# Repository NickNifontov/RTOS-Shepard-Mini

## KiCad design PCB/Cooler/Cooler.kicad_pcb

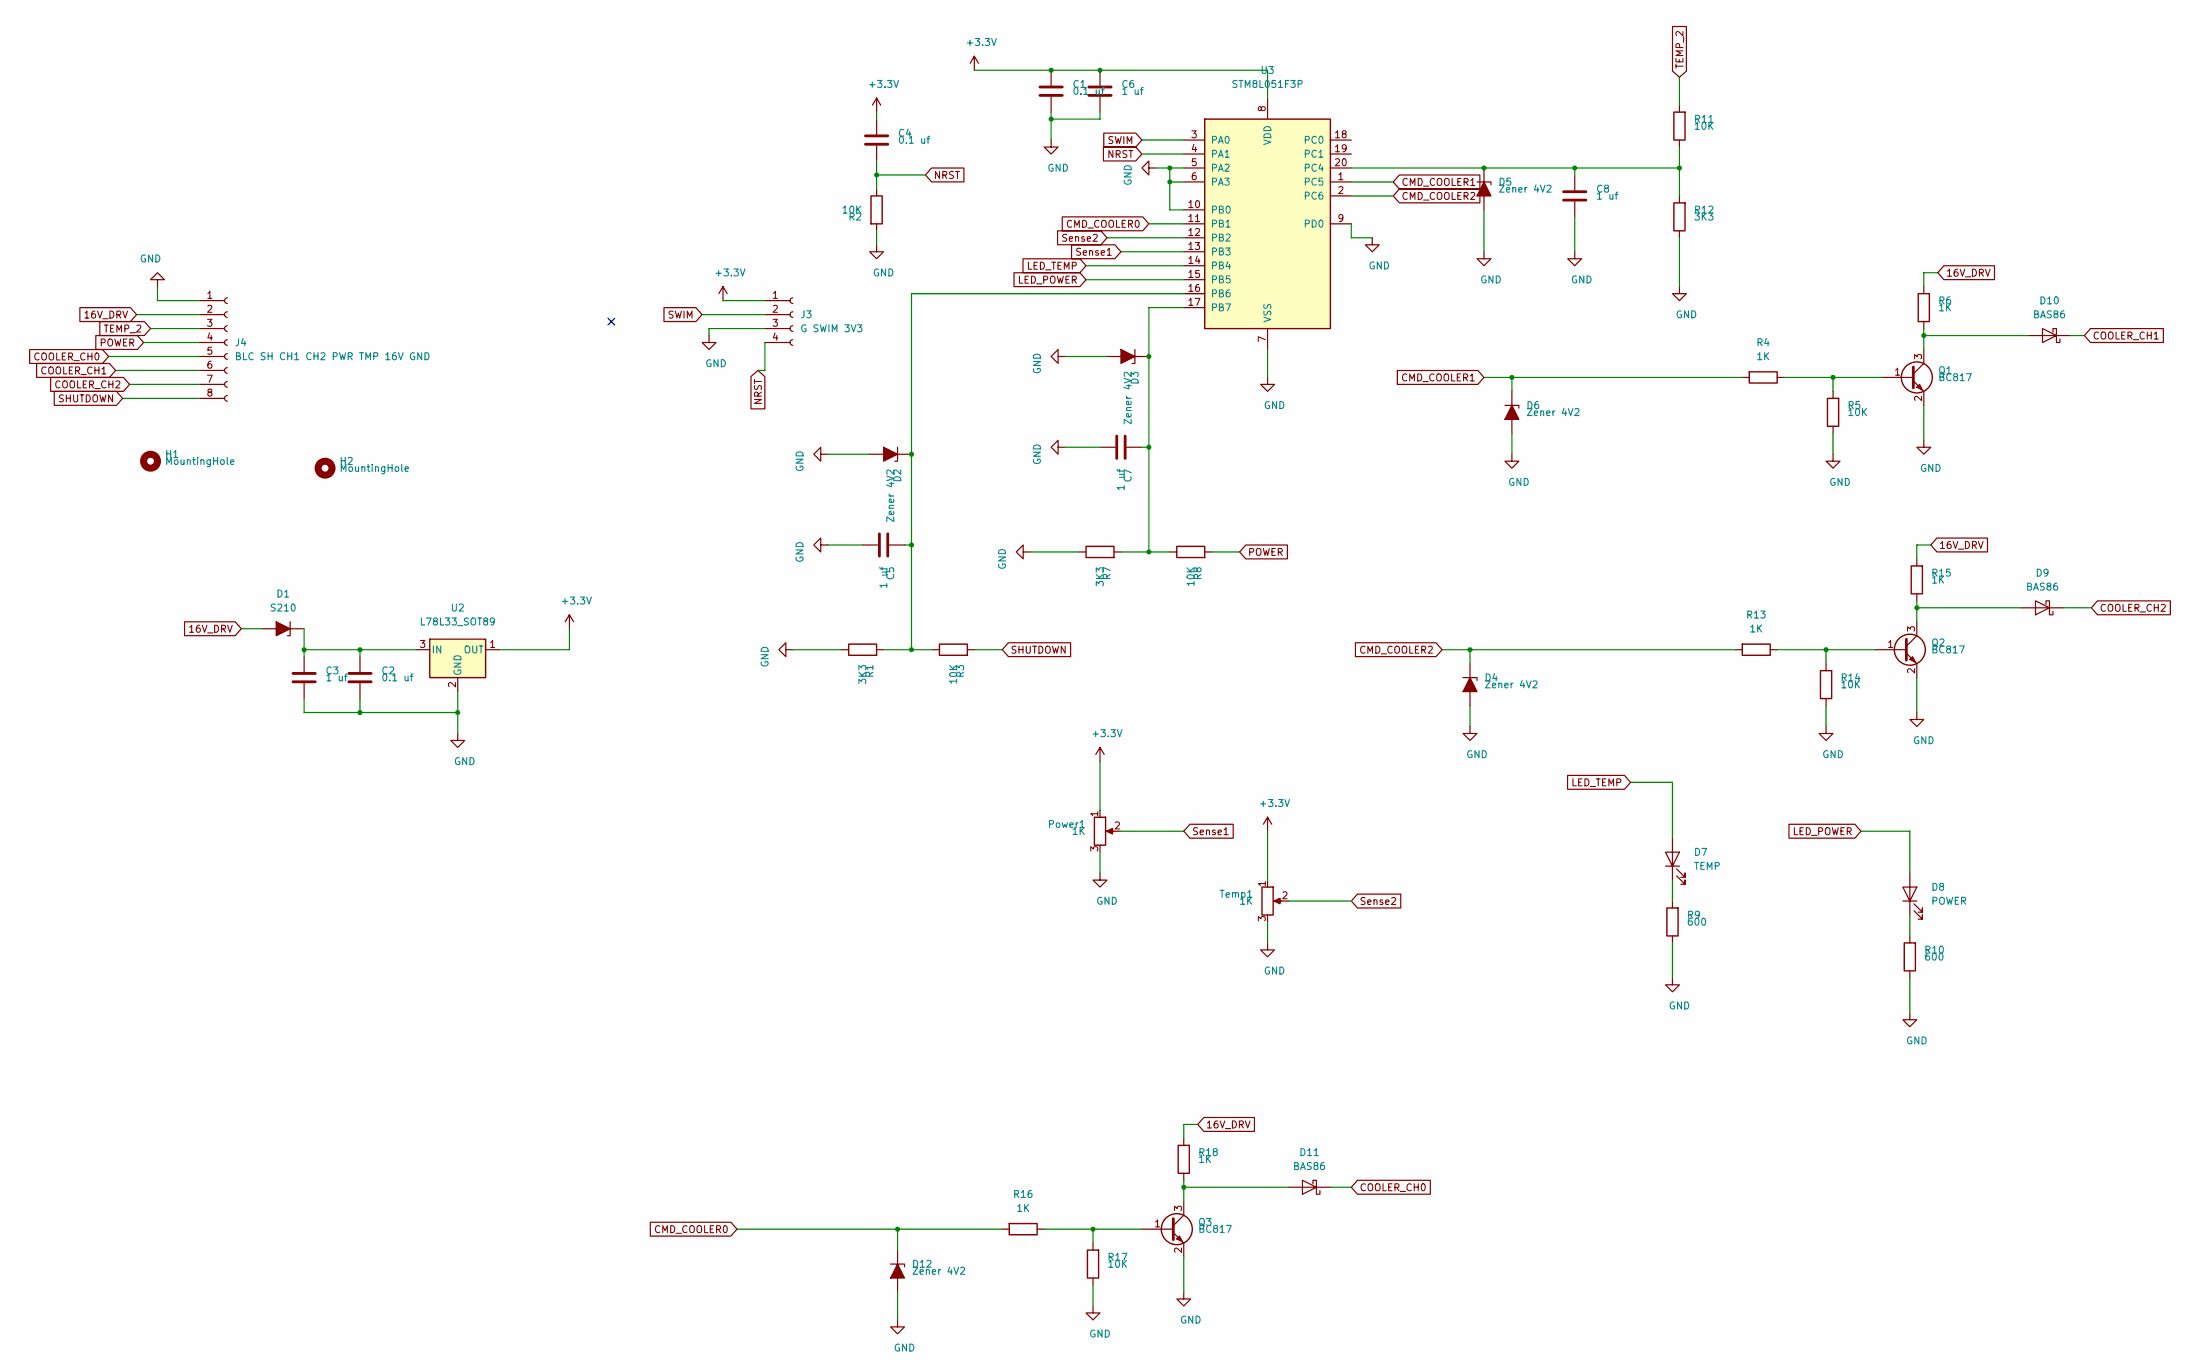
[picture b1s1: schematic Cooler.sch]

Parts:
C1, C2, C4: 0.1 uf; C_1206_3216Metric_Pad1.42x1.75mm_HandSolder
C3, C5, C6, C7, C8: 1 uf; C_1206_3216Metric_Pad1.42x1.75mm_HandSolder
D1: S210; D_SMB
D2, D3, D4, D5, D6, D12: Zener 4V2; D_MiniMELF
D7: TEMP; LED_1206_3216Metric_Pad1.42x1.75mm_HandSolder
D8: POWER; LED_1206_3216Metric_Pad1.42x1.75mm_HandSolder
D9, D10, D11: BAS86; D_MiniMELF
H1, H2: MountingHole; MountingHole_2.2mm_M2_ISO14580_Pad
J3: G SWIM 3V3; PinHeader_1x04_P2.54mm_Vertical
J4: BLC SH CH1 CH2 PWR TMP 16V GND; PinHeader_1x08_P2.54mm_Horizontal
Power1: 1K; Potentiometer_Bourns_3296W_Vertical
Q1, Q2, Q3: BC817; SOT-23
R1, R7, R12: 3K3; R_0805_2012Metric_Pad1.15x1.40mm_HandSolder
R2, R3, R5, R8, R11, R14, R17: 10K; R_0805_2012Metric_Pad1.15x1.40mm_HandSolder
R4, R6, R13, R15, R16, R18: 1K; R_0805_2012Metric_Pad1.15x1.40mm_HandSolder
R9, R10: 600; R_0805_2012Metric_Pad1.15x1.40mm_HandSolder
Temp1: 1K; Potentiometer_Bourns_3296W_Vertical
U2: L78L33_SOT89; SOT-89-3
U3: STM8L051F3P; TSSOP-20_4.4x6.5mm_P0.65mm

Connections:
16V_DRV: D1.2 (A), J4.2, R6.2, R15.2, R18.2
+3V3: C1.2, C4.2, C6.2, J3.1, Power1.1, Temp1.1, U2.1 (OUT), U3.8 (VDD)
CMD_COOLER0: D12.1 (K), R16.2, U3.11 (PB1)
CMD_COOLER1: D6.1 (K), R4.2, U3.1 (PC5)
CMD_COOLER2: D4.1 (K), R13.2, U3.2 (PC6)
COOLER_CH0: D11.1 (K), J4.5
COOLER_CH1: D10.1 (K), J4.6
COOLER_CH2: D9.1 (K), J4.7
GND: C1.1, C2.1, C3.1, C5.1, C6.1, C7.1, C8.1, D2.2 (A), D3.2 (A), D4.2 (A), D5.2 (A), D6.2 (A), D12.2 (A), J3.3, J4.1, Power1.3, Q1.2 (E), Q2.2 (E), Q3.2 (E), R1.1, R2.2, R5.1, R7.1, R9.1, R10.1, R12.1, R14.1, R17.1, Temp1.3, U2.2 (GND), U3.5 (PA2), U3.6 (PA3), U3.7 (VSS), U3.9 (PD0), U3.10 (PB0)
LED_POWER: D8.2 (A), U3.15 (PB5)
LED_TEMP: D7.2 (A), U3.14 (PB4)
NRST: C4.1, J3.4, R2.1, U3.4 (PA1)
unnamed: C2.2, C3.2, D1.1 (K), U2.3 (IN)
unnamed: C5.2, D2.1 (K), R1.2, R3.1, U3.16 (PB6)
unnamed: C7.2, D3.1 (K), R7.2, R8.1, U3.17 (PB7)
unnamed: C8.2, D5.1 (K), R11.1, R12.2, U3.20 (PC4)
unnamed: D7.1 (K), R9.2
unnamed: D8.1 (K), R10.2
unnamed: D9.2 (A), Q2.3 (C), R15.1
unnamed: D10.2 (A), Q1.3 (C), R6.1
unnamed: D11.2 (A), Q3.3 (C), R18.1
unnamed: Q1.1 (B), R4.1, R5.2
unnamed: Q2.1 (B), R13.1, R14.2
unnamed: Q3.1 (B), R16.1, R17.2
POWER: J4.4, R8.2
SHUTDOWN: J4.8, R3.2
SWIM: J3.2, U3.3 (PA0)
Sense1: Power1.2, U3.13 (PB3)
Sense2: Temp1.2, U3.12 (PB2)
TEMP_2: J4.3, R11.2

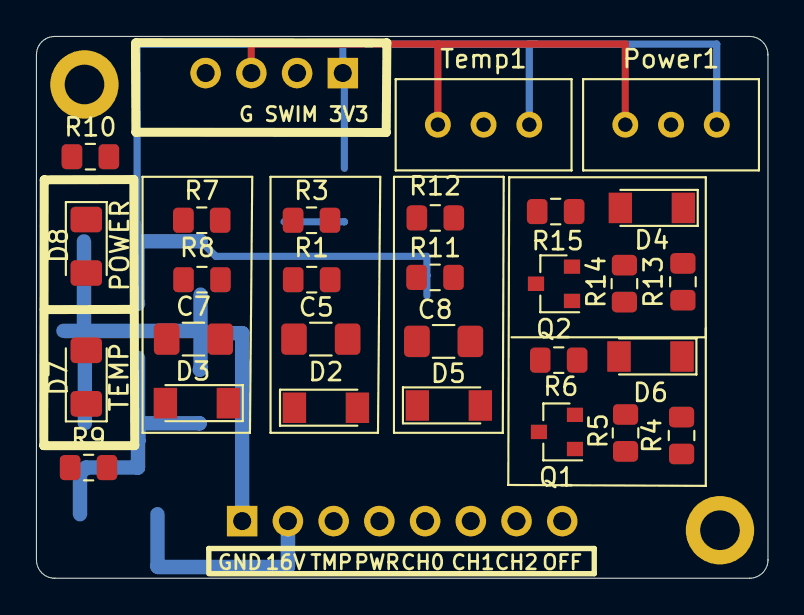
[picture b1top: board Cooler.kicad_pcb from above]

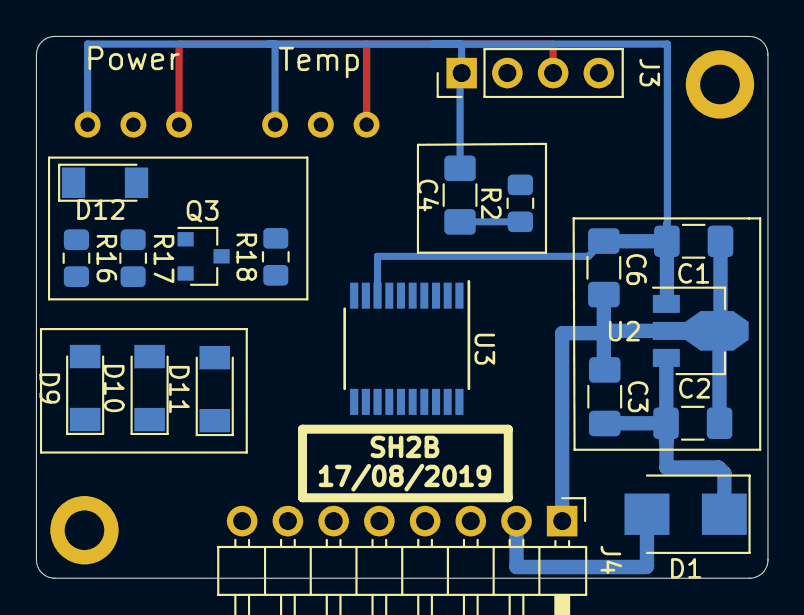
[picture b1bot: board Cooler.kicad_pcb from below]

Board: 2 copper layers, 40.6 x 30.1 mm, 49 parts (19 on the bottom side), 30 nets.

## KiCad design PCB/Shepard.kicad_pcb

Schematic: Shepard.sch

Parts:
BAT1: 1K; Potentiometer_Bourns_3296W_Vertical
BAT2: SLOW_C; Potentiometer_Bourns_3296W_Vertical
BZ1: Buzzer; Buzzer_12x9.5RM7.6
BZ2: Buzzer; Buzzer_TDK_PS1240P02BT_D12.2mm_H6.5mm
BZ3: Buzzer; MagneticBuzzer_Kingstate_KCG0601
C1, C10: 33uf 100V; CP_Radial_D8.0mm_P5.00mm
C2, C7, C14, C15: 10uf; C_1206_3216Metric_Pad1.42x1.75mm_HandSolder
C3, C4, C5, C6, C8, C9, C11, C26, C28: 0.1uf; C_1206_3216Metric_Pad1.42x1.75mm_HandSolder
C12: 10 uf; CP_Radial_D5.0mm_P2.50mm
C13: 10 uf; C_Elec_5x5.4
C16: 0.1uf 100V; C_1206_3216Metric_Pad1.42x1.75mm_HandSolder
C17: 33nf; C_1206_3216Metric_Pad1.42x1.75mm_HandSolder
C18: 1uf; C_1206_3216Metric_Pad1.42x1.75mm_HandSolder
C19, C20: 100uf 25v; CP_Radial_D8.0mm_P5.00mm
C21: 100pf; C_1206_3216Metric_Pad1.42x1.75mm_HandSolder
C23, C30: 33uf 100v; C_Elec_10x10.2
C24, C25: 220uf 25v; C_Elec_8x10.2
CURRENT2: 1K; Potentiometer_Bourns_3296W_Vertical
D1, D5, D7, D10, D49: Zener 4V2; D_1206_3216Metric_Pad1.42x1.75mm_HandSolder
D2, D11, D32, D38: BAS86; D_MiniMELF
D6: XL7015; TO-252-5_TabPin3
D9, D12: S210; D_SMB
D13: CUR; LED_1206_3216Metric_Pad1.42x1.75mm_HandSolder
D15: BLOCK; LED_1206_3216Metric_Pad1.42x1.75mm_HandSolder
D17: STAT; LED_1206_3216Metric_Pad1.42x1.75mm_HandSolder
D20: smbj20A; D_SMB
D28, D29, D30, D31, D33, D34, D35, D36: US1B; D_SMA
H1, H2, H3, H4: MountingHole; MountingHole_2.2mm_M2_DIN965_Pad
H5: MountingHole_Pad; MountingHole_2.2mm_M2_DIN965_Pad
J1: ADC RAW G; PinHeader_1x03_P2.54mm_Horizontal
J2: COIL_PORT; PinHeader_2x03_P2.54mm_Horizontal
J3: ON/OFF; PinHeader_1x02_P2.54mm_Horizontal
J4: 3V3 DIO CLK G; PinHeader_1x04_P2.54mm_Vertical
J5: TO_PLATKAR; PinHeader_1x07_P2.54mm_Horizontal
J8: TO BOOSTER; PinHeader_1x07_P2.54mm_Horizontal
L1: 47uf; L_Radial_D8.7mm_P5.00mm_Fastron_07HCP
L2: 47uf; L_12x12mm_H8mm
L3: bead; L_0805_2012Metric_Pad1.15x1.40mm_HandSolder
Q1, Q2, Q4, Q6, Q7, Q8, Q10: BC817; SOT-23_Handsoldering
Q9, Q11: BCX53; SOT-89-3
R1, R5, R12, R19, R20, R21, R26, R32, R45, R53, R54, R56, R57, R59, R60, R62, R64, R65, R70: 1K; R_1206_3216Metric_Pad1.42x1.75mm_HandSolder
R2: 330-380; R_1206_3216Metric_Pad1.42x1.75mm_HandSolder
R3, R15: 20; R_1206_3216Metric_Pad1.42x1.75mm_HandSolder
R4: R0; R_0805_2012Metric_Pad1.15x1.40mm_HandSolder
R6: 10k; R_1206_3216Metric_Pad1.42x1.75mm_HandSolder
R7: 3.3K-3.8K; R_1206_3216Metric_Pad1.42x1.75mm_HandSolder
R8: 20K; R_1206_3216Metric_Pad1.42x1.75mm_HandSolder
R9, R11, R13: 5K; R_1206_3216Metric_Pad1.42x1.75mm_HandSolder
R10: 100k; R_1206_3216Metric_Pad1.42x1.75mm_HandSolder
R14, R51: 100; R_1206_3216Metric_Pad1.42x1.75mm_HandSolder
R16: 4K7; R_1206_3216Metric_Pad1.42x1.75mm_HandSolder
R17, R18, R22, R23, R47, R52, R55, R58, R61, R63, R66, R67: 10K; R_1206_3216Metric_Pad1.42x1.75mm_HandSolder
R24, R68: 100K; R_1206_3216Metric_Pad1.42x1.75mm_HandSolder
R25: 1K8; R_1206_3216Metric_Pad1.42x1.75mm_HandSolder
R27: 30K; R_1206_3216Metric_Pad1.42x1.75mm_HandSolder
R28: 1K6; R_1206_3216Metric_Pad1.42x1.75mm_HandSolder
R29: 1K2; R_1206_3216Metric_Pad1.42x1.75mm_HandSolder
R30, R31, R33, R37, R40, R43: 20; R_2512_6332Metric_Pad1.52x3.35mm_HandSolder
R34, R49: 0; R_1206_3216Metric_Pad1.42x1.75mm_HandSolder
R44, R48, R71: 300-600; R_1206_3216Metric_Pad1.42x1.75mm_HandSolder
U1: LM317_3PinPackage; TO-252-2
U2: STM32L031F6Px; TSSOP-20_4.4x6.5mm_P0.65mm
U4: PC817; DIP-4_W7.62mm

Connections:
15V1_OK: J5.1, Q9.2 (C)
15V2_OK: J8.6, Q11.2 (C)
16V_ADC: C6.1, D7.1 (K), R18.2, R26.1, R34.1, U2.10 (PA4)
+15V: C7.1, C8.2, C17.2, C18.2, C19.1, C20.1, C24.1, C25.1, L1.2, L2.2, Q9.3 (E), Q11.3 (E), R3.2, R15.1, R18.1, R23.1, R27.2, R60.1, R65.1, R70.2, U1.3 (VI)
+48V: C1.1, C10.1, C16.2, C23.1, C30.1, D6.1 (VIN), D9.1 (K), R4.1, R17.1
AB: BAT1.2, C3.1, D10.1 (K), U2.7 (PA1)
AB_RAW: J1.1, R4.2, R8.1
BLOCK_PORT: R21.1, U2.12 (PA6)
BLOCK_PORT_2: R5.2, R54.2, U2.13 (PA7)
BLOCK_POWER: R57.2, R62.2, R71.2, U2.14 (PB1)
BLOCK_PU: D11.1 (K), J5.5, R24.1
BUZZER: R20.1, U2.3 (PC15)
CLK: J4.2, R66.2, U2.20 (PA14)
COIL1_A: D28.2 (A), D29.1 (K), J2.1
COIL1_A_OUT: D28.1 (K), D30.1 (K), D32.2 (A), R30.1, R31.1, R33.1
COIL1_B: D30.2 (A), D31.1 (K), J2.2
COIL1_B_OUT: BAT2.3, C1.2, C2.2, C3.2, C4.1, C5.2, C6.2, C7.2, C8.1, C9.1, C10.2, C11.2, C12.2, C13.2, C14.2, C15.1, C16.1, C18.1, C19.2, C20.2, C21.2, C23.2, C24.2, C25.2, C26.2, C28.2, C30.2, D1.2 (A), D5.2 (A), D6.3 (GND), D7.2 (A), D10.2 (A), D12.2 (A), D13.1 (K), D15.1 (K), D17.1 (K), D20.2 (A), D29.2 (A), D31.2 (A), D34.2 (A), D36.2 (A), D49.2 (A), J1.3, J3.1, J4.1, J5.2, J8.7, Q1.2 (E), Q2.2 (E), Q4.2 (E), Q6.2 (E), Q7.2 (E), Q8.2 (E), Q10.2 (E), R2.2, R7.2, R10.2, R11.2, R12.1, R14.2, R19.2, R24.2, R25.2, R26.2, R30.2, R31.2, R32.1, R33.2, R37.2, R40.2, R43.2, R51.2, R58.1, R63.1, R66.1, R68.1, U2.15 (VSS), U4.2, U4.3
COIL2_A: D33.2 (A), D34.1 (K), J2.3
COIL2_A_OUT: D33.1 (K), D35.1 (K), D38.2 (A), R37.1, R40.1, R43.1
COIL2_B: D35.2 (A), D36.1 (K), J2.4
COOLER_1: R45.2, U2.11 (PA5)
COOLER_1_OUT: J8.5, Q4.3 (C), R70.1
CURRENT: C28.1, D49.1 (K), R6.2, R7.1, U2.6 (PA0)
DIO: J4.3, R61.1, U2.19 (PA13)
EX_A: D2.2 (A), J2.5, J2.6
KLAPAN_COMP: C21.1, D1.1 (K), R1.2, R2.1, U2.9 (PA3)
LED: R44.2, U2.17 (PA9)
LED_2: R48.2, U2.18 (PA10)
NRST: C26.1, R67.1, U2.4 (NRST)
unnamed: BAT1.1, R8.2
unnamed: BAT1.3, R14.1
unnamed: BAT2.2, R34.2
unnamed: BZ1.1 (-), BZ2.1 (-), BZ3.1 (-), R15.2
unnamed: BZ1.2 (+), BZ2.2 (+), BZ3.2 (+), Q1.3 (C)
unnamed: C11.1, C15.2, L3.1, U2.5 (VDDA)
unnamed: CURRENT2.1, R49.2
unnamed: CURRENT2.3, R51.1
unnamed: D11.2 (A), Q2.3 (C), R23.2
unnamed: D6.2 (SW), D12.1 (K), L1.1, L2.1
unnamed: D13.2 (A), R48.1
unnamed: D15.2 (A), R71.1
unnamed: D17.2 (A), R44.1
unnamed: D9.2 (A), D20.1 (K), J1.2
unnamed: J8.2, R3.1
unnamed: Q1.1 (B), R19.1, R20.2
unnamed: Q2.1 (B), R21.2, R22.2
unnamed: Q4.1 (B), R45.1, R47.2
unnamed: Q6.1 (B), R5.1, R52.2
unnamed: Q7.1 (B), R54.1, R55.2
unnamed: Q8.1 (B), R57.1, R58.2
unnamed: Q8.3 (C), R59.2
unnamed: Q9.1 (B), R59.1, R60.2
unnamed: Q10.1 (B), R62.1, R63.2
unnamed: Q10.3 (C), R64.2
unnamed: Q11.1 (B), R64.1, R65.2
unnamed: R11.1, R13.1, U4.1
unnamed: R25.1, R29.2, U1.1 (ADJ)
unnamed: R28.1, R32.2
unnamed: R68.2, U2.1 (BOOT0)
PEREKLUCHALKA: J5.6, R13.2
POLKA_SUMATOR: D2.1 (K), D32.1 (K), D38.1 (K), H5.1, R49.1
POLKA_TO_PU_READY: CURRENT2.2, J5.7, R1.1, R6.1, R10.1
PWM1: J5.4, R56.2
PWM1-OUT: J8.3, Q7.3 (C), R56.1
PWM2: J5.3, R53.2
PWM2-OUT: J8.4, Q6.3 (C), R53.1
SD: R16.2, U2.2 (PC14), U4.4
TEMP_2: J8.1, R9.2
TEMP_ADC: C5.1, D5.1 (K), R9.1, R12.2, U2.8 (PA2)
XL_EN: D6.5 (EN), J3.2, R17.2
XL_FB: C17.1, D6.4 (FB), R27.1, R28.2

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
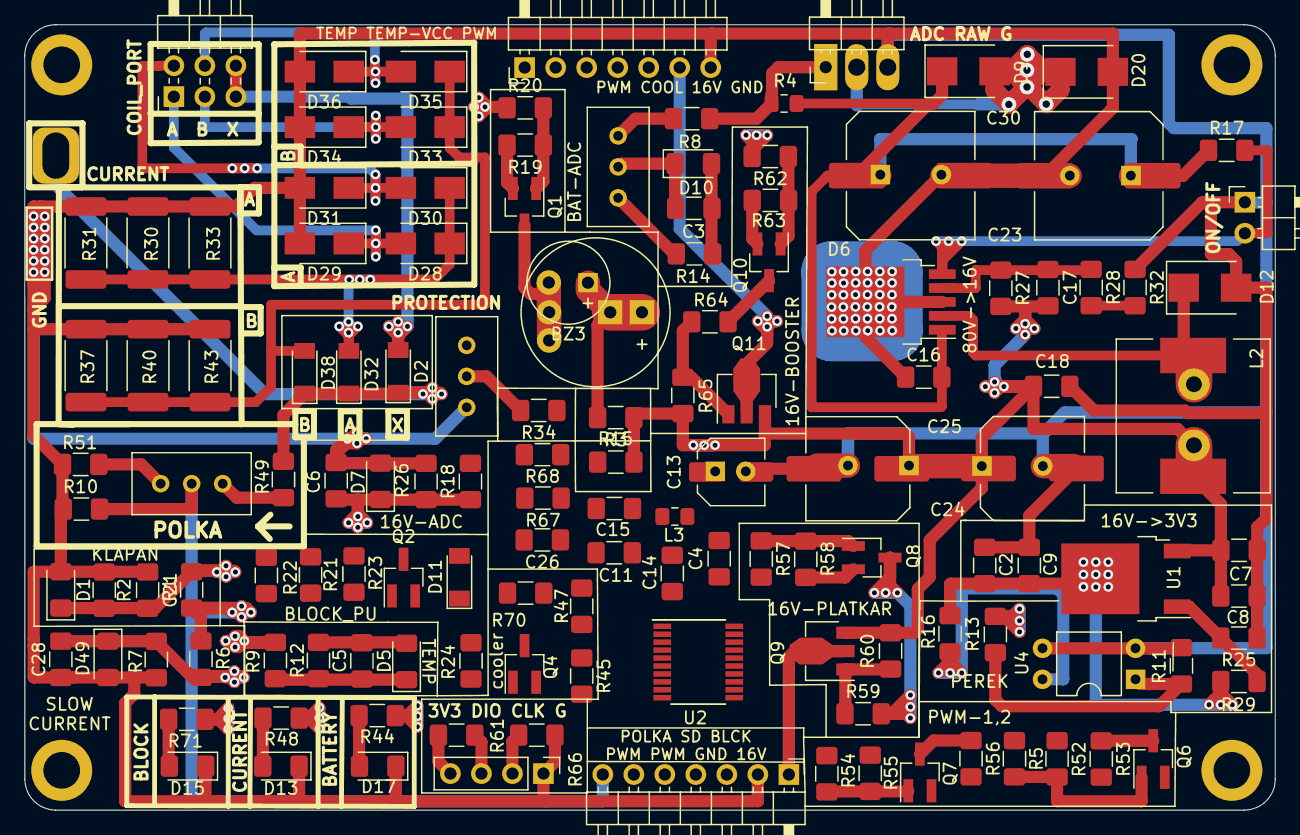
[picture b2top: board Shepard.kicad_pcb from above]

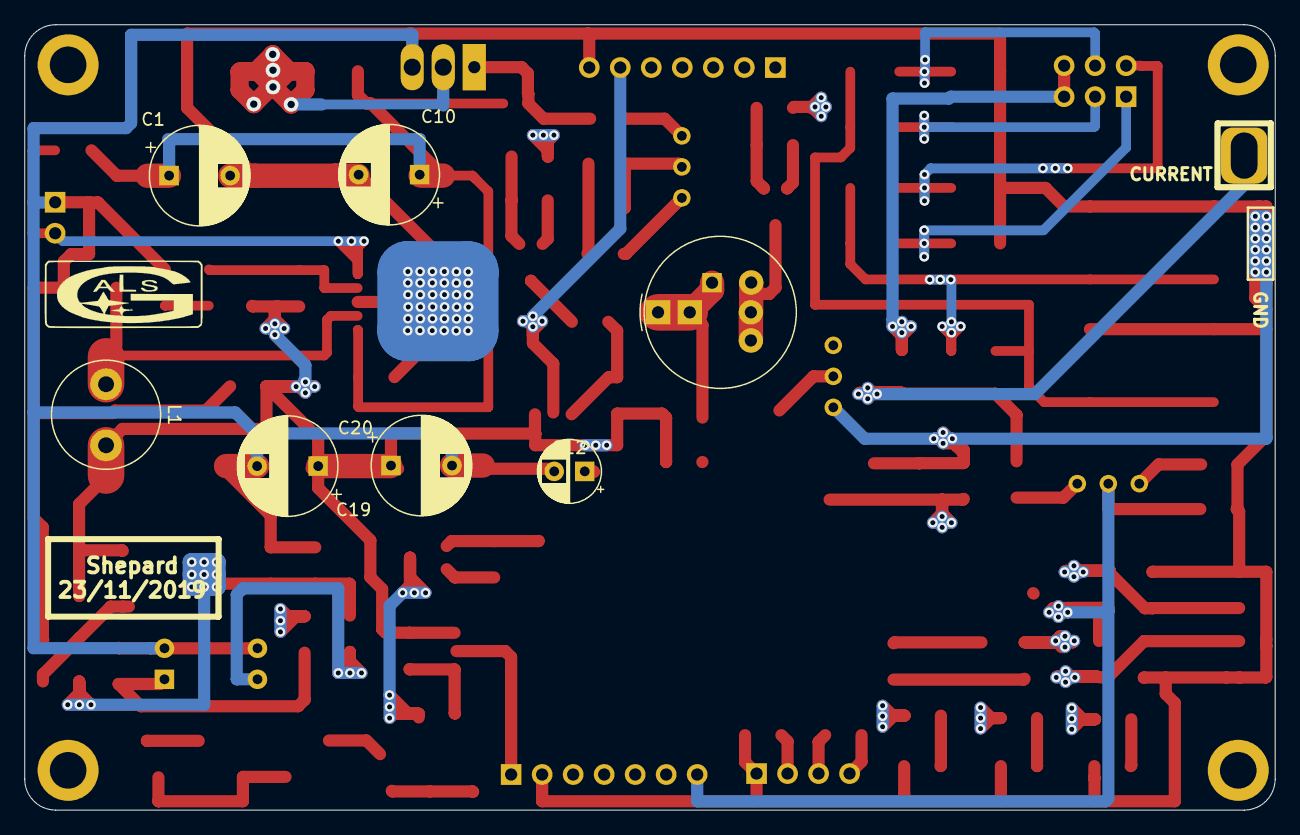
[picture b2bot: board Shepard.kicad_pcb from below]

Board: 2 copper layers, 102.4 x 64.3 mm, 145 parts (7 on the bottom side), 72 nets.

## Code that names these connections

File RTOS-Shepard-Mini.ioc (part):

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Mcu.Name=STM32L031F(4-6)Px
Mcu.Package=TSSOP20
Mcu.UserName=STM32L031F6Px
PA0-CK_IN.GPIOParameters=GPIO_Label
PA0-CK_IN.GPIO_Label=CURRENT
PA0-CK_IN.Mode=IN0
PA0-CK_IN.Signal=ADC_IN0
PA1.GPIOParameters=GPIO_Label
PA1.GPIO_Label=AB
PA1.Mode=IN1
PA1.Signal=ADC_IN1
PA10.GPIOParameters=GPIO_Label
PA10.GPIO_Label=LED_2
PA10.Signal=GPIO_Output
PA13.GPIOParameters=GPIO_Label
PA13.GPIO_Label=SWDIO
PA13.Mode=Serial_Wire
PA13.Signal=SYS_SWDIO
PA14.GPIOParameters=GPIO_Label
PA14.GPIO_Label=SWCLK
PA14.Mode=Serial_Wire
PA14.Signal=SYS_SWCLK
PA2.GPIOParameters=GPIO_Label
PA2.GPIO_Label=TEMP_ADC
PA2.Mode=IN2
PA2.Signal=ADC_IN2
PA3.GPIOParameters=GPIO_Label
PA3.GPIO_Label=KLAPAN_COMP
PA3.Mode=INP
PA3.Signal=COMP2_INP
PA4.GPIOParameters=GPIO_Label
PA4.GPIO_Label=VCC16V
PA4.Mode=IN4
PA4.Signal=ADC_IN4
PA5.GPIOParameters=GPIO_Speed,GPIO_Label
PA5.GPIO_Label=Cooler
PA5.GPIO_Speed=GPIO_SPEED_FREQ_VERY_HIGH
PA5.Signal=S_TIM2_CH1
PA6.GPIOParameters=GPIO_Speed,PinState,GPIO_Label
PA6.GPIO_Label=BLOCK_PORT_1
PA6.GPIO_Speed=GPIO_SPEED_FREQ_VERY_HIGH
PA6.PinState=GPIO_PIN_SET
PA6.Signal=GPIO_Output
PA7.GPIOParameters=GPIO_Speed,PinState,GPIO_Label
PA7.GPIO_Label=BLOCK_PORT_2
PA7.GPIO_Speed=GPIO_SPEED_FREQ_VERY_HIGH
PA7.PinState=GPIO_PIN_SET
PA7.Signal=GPIO_Output
PA9.GPIOParameters=GPIO_Label
PA9.GPIO_Label=LED_1
PA9.Signal=GPIO_Output
PB1.GPIOParameters=GPIO_Speed,GPIO_Label
PB1.GPIO_Label=BLOCK_POWER
PB1.GPIO_Speed=GPIO_SPEED_FREQ_VERY_HIGH
PB1.Signal=GPIO_Output
PC14-OSC32_IN.GPIOParameters=GPIO_Label,GPIO_ModeDefaultEXTI
PC14-OSC32_IN.GPIO_Label=SD
PC14-OSC32_IN.GPIO_ModeDefaultEXTI=GPIO_MODE_IT_RISING_FALLING
PC14-OSC32_IN.Signal=GPXTI14
PC15-OSC32_OUT.GPIOParameters=PinState,GPIO_Label
PC15-OSC32_OUT.GPIO_Label=BUZZER
PC15-OSC32_OUT.PinState=GPIO_PIN_RESET
PC15-OSC32_OUT.Signal=GPIO_Output
RCC.HSE_VALUE=8000000
RCC.SYSCLKFreq_VALUE=2097000
board=custom

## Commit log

2019-11-03 first release
2019-11-10 First release of 0.1 version :o)
2019-11-11 added SLOW protection
2019-11-11 version 0.2
2019-11-12 comp2 speed up
2019-11-14 0.2 version
2019-11-14 0.21 version
2019-11-15 rev 0.3
2019-12-08 added PCB
